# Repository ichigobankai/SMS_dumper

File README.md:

# SMS dumper

This project is a very low cost USB reader/writer(1) for Sega Master System cartridges.
HID code is based on libopencm3 ARM Lib & paulfertser/stm32-tx-hid ( https://github.com/paulfertser/stm32-tx-hid)

Support :
* Sega Master System mapper (Sms/Mark3, SG-1000/SC-3000/Othello Multivision)
* Codemasters mapper
* Korean "large" mapper (type Jang Pung III)
* Read and write S-ram (Master System Mapper)
* can re-write flash eprom on my pcb(1)

Speed (can vary depend on USB) :
* Dump 128kB : 4s
* write 128kB : 21s (erase/write and verif)(1)

(1)only working with my sega mapper clone/pcb

This firmware is targetting the cheapest STM32F103 board as found in
numerous listings on eBay and Aliexpress (might have the following
keywords: ARM STM32F103C8T6 Minimum System Development Board Module
For Arduino).

* Board description
The board has an STM32F103C8T6 controller for USB communication
(no drivers needed, connected in HID) 
It uses two 74LS273 for multiplexing i/o data lines into address lines.

* Building the firmware
After cloning the repository "git submodule init; git submodule
update" needs to be run once, then "build.sh" to build everything
necessary.

It is assumed that "arm-none-eabi" toolchain is available in PATH,
"GCC ARM Embedded" is the recommended option. In case you need to
specify a path, CROSS_COMPILE make variable should be set
appropriately.

* Initial flashing procedure
There're two ways of flashing a blank board: via SWD and via serial
bootloader. For the first method a suitable debug adapter is needed
(e.g. ST-Link or J-Link), for the second one can use just about any
USB-UART bridge (the only requirement that is a bit unusual is to
support "even" parity).

The image to be flashed is "smsdumper_stm32_bootANDsoft.bin", it
contains both a DFU-compliant bootloader and the main firmware. 

If you have any suggestions or questions, feel free to contact me
directly via email.

Ichigo <github@ultimate-consoles.fr>

My friend X-death have made a silimar dumper but for Megadrive/Genesis (Md Dumper)

Available on his Github page : https://github.com/X-death25/STM32_Projects/tree/master/Megadrive_HID

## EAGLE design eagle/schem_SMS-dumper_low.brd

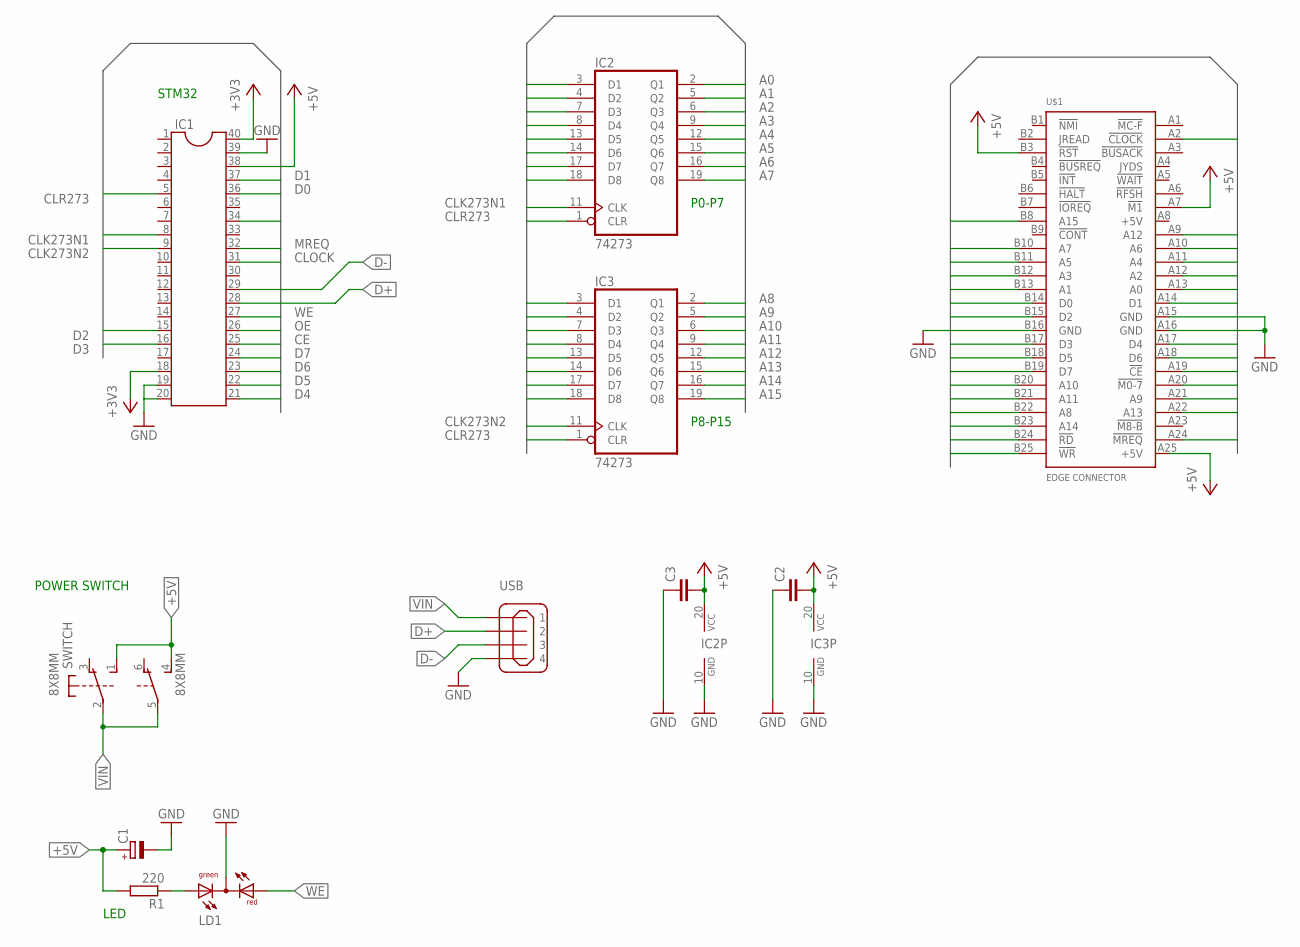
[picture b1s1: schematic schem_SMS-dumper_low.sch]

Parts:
8X8MM: SWITCH; PVA2F
C1: CPOL-EUE2,5-6E; E2,5-6E
C2, C3: C-EU050-024X044; C050-024X044
IC1: DIL40
IC2, IC3: 74273; DIL20
LD1: DUOLED-RG-C; DUOLED-C-5MM
R1: 220; 0204/7
U$1: EDGE CONNECTOR; CARD50F
USB: MINI-USB_4P-85-32004-10X; 85-32004-10X

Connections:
+3V3: IC1.18, IC1.40
+5V: 8X8MM.1 (S), 8X8MM.4 (S), C1.+, C2.2, C3.2, IC1.38, IC2.20 (VCC), IC3.20 (VCC), R1.2, U$1.A7 (!M1), U$1.A25 (+5V), U$1.B3 (!RST)
A0: IC2.2 (Q1), U$1.A13 (A0)
A1: IC2.5 (Q2), U$1.B13 (A1)
A2: IC2.6 (Q3), U$1.A12 (A2)
A3: IC2.9 (Q4), U$1.B12 (A3)
A4: IC2.12 (Q5), U$1.A11 (A4)
A5: IC2.15 (Q6), U$1.B11 (A5)
A6: IC2.16 (Q7), U$1.A10 (A6)
A7: IC2.19 (Q8), U$1.B10 (A7)
A8: IC3.2 (Q1), U$1.B22 (A8)
A9: IC3.5 (Q2), U$1.A21 (A9)
A10: IC3.6 (Q3), U$1.B20 (A10)
A11: IC3.9 (Q4), U$1.B21 (A11)
A12: IC3.12 (Q5), U$1.A9 (A12)
A13: IC3.15 (Q6), U$1.A22 (A13)
A14: IC3.16 (Q7), U$1.B23 (A14)
A15: IC3.19 (Q8), U$1.B8 (A15)
CE: IC1.25, U$1.A19 (!CE)
CLK273N1: IC1.8, IC2.11 (CLK)
CLK273N2: IC1.9, IC3.11 (CLK)
CLOCK: IC1.31, U$1.A2 (!CLOCK)
CLR273: IC1.5, IC2.1 (CLR), IC3.1 (CLR)
D0: IC1.36, IC2.3 (D1), IC3.3 (D1), U$1.B14 (D0)
D1: IC1.37, IC2.4 (D2), IC3.4 (D2), U$1.A14 (D1)
D2: IC1.15, IC2.7 (D3), IC3.7 (D3), U$1.B15 (D2)
D3: IC1.16, IC2.8 (D4), IC3.8 (D4), U$1.B17 (D3)
D4: IC1.21, IC2.13 (D5), IC3.13 (D5), U$1.A17 (D4)
D5: IC1.22, IC2.14 (D6), IC3.14 (D6), U$1.B18 (D5)
D6: IC1.23, IC2.17 (D7), IC3.17 (D7), U$1.A18 (D6)
D7: IC1.24, IC2.18 (D8), IC3.18 (D8), U$1.B19 (D7)
D+: IC1.28, USB.2
D-: IC1.29, USB.3
GND: C1.-, C2.1, C3.1, IC1.19, IC1.20, IC1.39, IC2.10 (GND), IC3.10 (GND), U$1.A15 (GND), U$1.A16 (GND), U$1.B16 (GND), USB.4
M0-7: IC1.34, U$1.A20 (!M0-7)
MREQ: IC1.32, U$1.A24 (!MREQ)
unnamed: LD1.AX (AG), R1.1
OE: IC1.26, U$1.B24 (!RD)
VIN: 8X8MM.2, 8X8MM.5, USB.1
WE: IC1.27, LD1.AR, U$1.B25 (!WR)

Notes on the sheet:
STM32
P0-P7
P8-P15
POWER SWITCH
LED

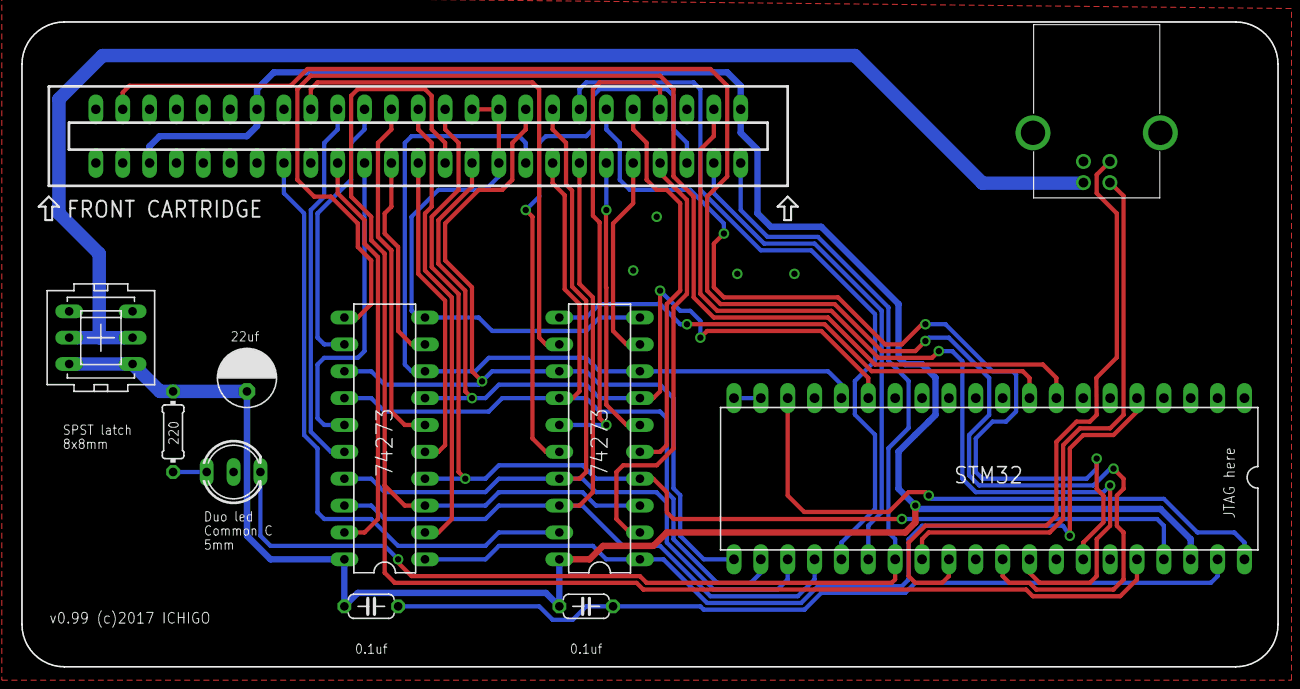
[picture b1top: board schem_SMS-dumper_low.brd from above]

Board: 2 copper layers, 118.7 x 61.0 mm, 11 parts (0 on the bottom side), 40 nets.

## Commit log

2017-05-31 Update Makefile
    upd CFLAGS for Linux
2017-05-31 Add files via upload
    linux Deb64

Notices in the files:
eagle/schem_SMS-dumper_low.brd:
v0.99 (c)2017 ICHIGO
